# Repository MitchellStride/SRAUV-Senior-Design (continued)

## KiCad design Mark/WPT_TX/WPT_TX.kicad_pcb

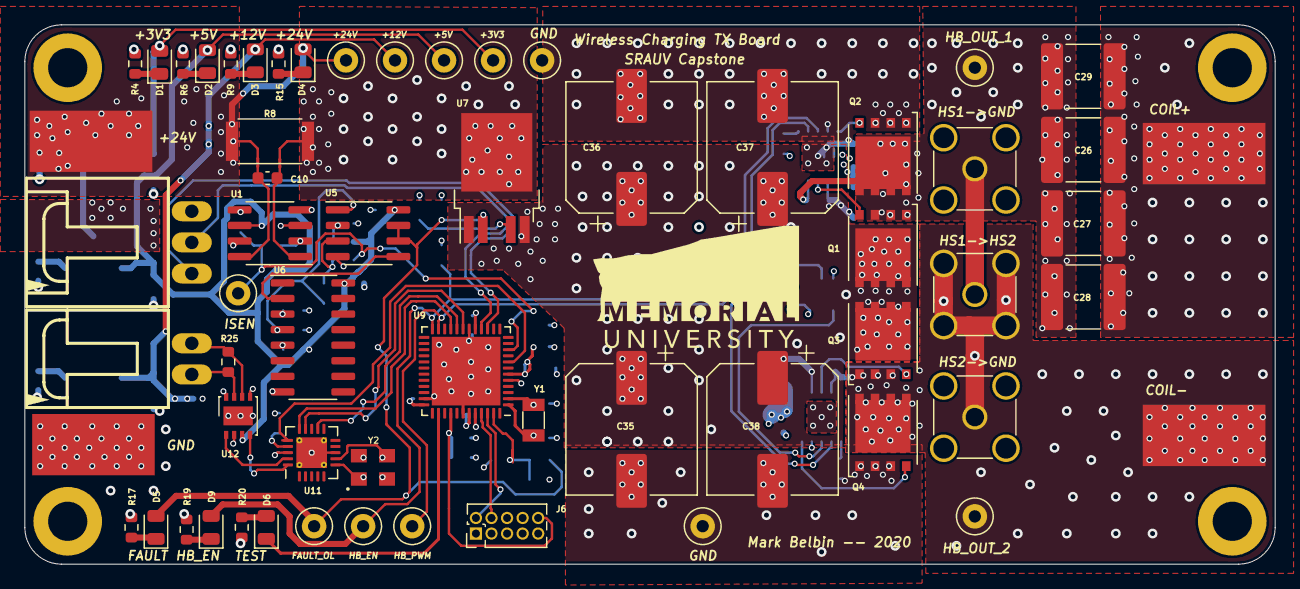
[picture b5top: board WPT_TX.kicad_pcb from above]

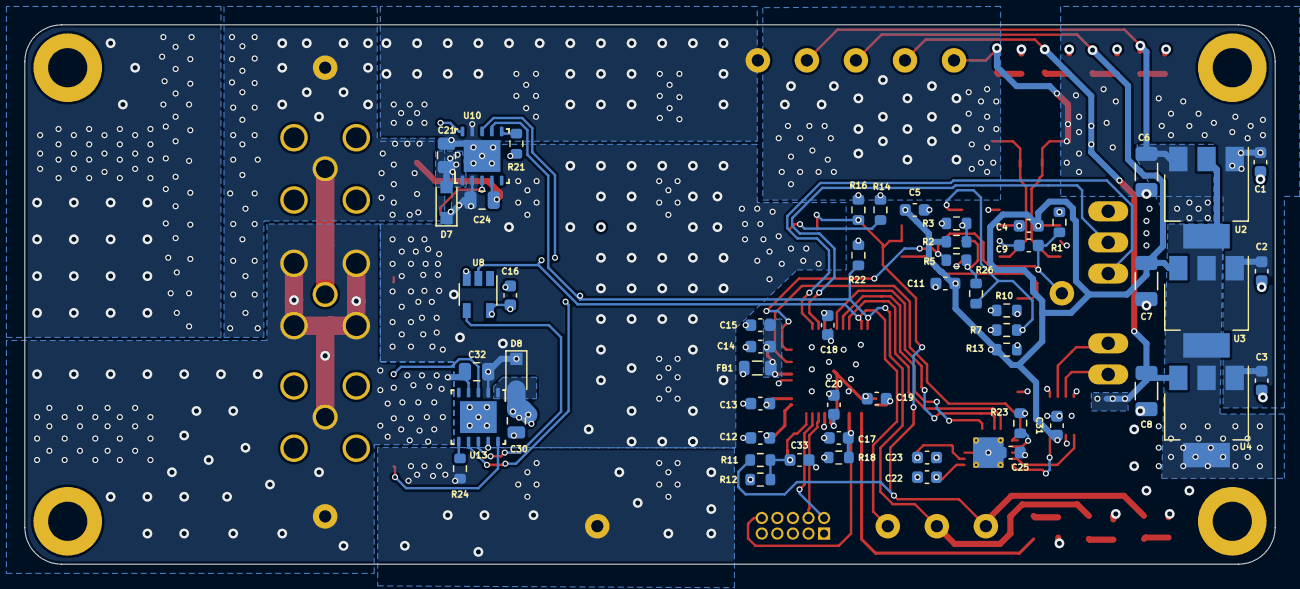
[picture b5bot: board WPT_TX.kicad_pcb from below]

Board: 4 copper layers, 102.0 x 44.0 mm, 121 parts (54 on the bottom side), 60 nets.

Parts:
C1, C2, C3, C4, C5, C9, C11, C14, C16, C17, C18, C19, C20, C25, C31, C33: 0.1u; C_0603_1608Metric
C6, C7, C8: 10u; C_1206_3216Metric
C10, C12, C13, C22, C23: 22p; C_0603_1608Metric
C15: 10u; C_0603_1608Metric
C21, C30: 0.47u; C_0805_2012Metric
C24, C32: 33n; C_0805_2012Metric
C26, C27, C28, C29: 100n; C_2220_5650Metric
C35, C36, C37, C38: 330u; CP_Elec_10x12.5
D1, D9: GREEN; LED_0805_2012Metric
D2: ORANGE; LED_0805_2012Metric
D3, D4: BLUE; LED_0805_2012Metric
D5: RED; LED_0805_2012Metric
D6: Orange; LED_0805_2012Metric
D7, D8: D_Schottky; D_SOD-323_HandSoldering
FB1: FB; L_0805_2012Metric
H1, H2, H3, H4: M3; MountingHole_3.2mm_M3_DIN965_Pad
J1, J2, J9, J10: Conn_01x01; SolderWirePad_single_SMD_5x10mm
J3, J4, J5: Conn_Coaxial; SMA_Amphenol_901-144_Vertical
J6: Conn_02x05_Odd_Even; PinHeader_2x05_P1.27mm_Vertical
J7: Conn_01x03; 70553-03
J8: Conn_01x04; 70553-02
NT1, NT2: Net-Tie_2; NetTie-2_SMD_Pad0.25mm
Q1, Q2, Q3, Q4: NMOS; TDSON-8-1
R1, R15: 2k; R_0603_1608Metric
R2, R7, R10, R11, R12, R13, R18, R21, R22, R23, R24, R26: 10k; R_0603_1608Metric
R3: 12k; R_0603_1608Metric
R4: 330; R_0603_1608Metric
R5, R9, R14, R16, R20: 1k; R_0603_1608Metric
R6, R17, R19: 680; R_0603_1608Metric
R8: 0.005; R_2512_Sense
R25: 120; R_0603_1608Metric
TP1, TP2, TP3, TP4, TP5, TP6, TP7, TP8, TP9, TP10, TP12, TP13: TestPoint; TestPoint_Loop_D1.80mm_Drill1.0mm_Beaded
U1: INA240A1D; SOIC-8_3.9x4.9mm_P1.27mm
U2: LM2937IMP-3.3; SOT-223-3_TabPin2
U3: LM2936-5.0; SOT-223-3_TabPin2
U4: LM2937IMP-12; SOT-223-3_TabPin2
U5: LMC6032; SOIC-8_3.9x4.9mm_P1.27mm
U6: CD4043BDR; SOIC-16_3.9x9.9mm_P1.27mm
U7: BTS6142DAUMA1; TO-252-4
U8: SN74LVC1G14DBV; TSOT-23-5
U9: ATSAMD21G16B-MFT; QFN-48-1EP_7x7mm_P0.5mm_EP5.6x5.6mm
U10, U13: LM5106; LM5106SD
U11: MCP2515-QFN20; QFN-20-1EP_4x4mm_P0.5mm_EP2.5x2.5mm_ThermalVias
U12: MCP2562-E-MF; DFN-8-1EP_3x3mm_P0.65mm_EP1.55x2.4mm
U14: Munlogo; MUNLOGO
Y1: 32.7680kHz; Crystal_SMD_3215-2pin_3.2x1.5mm
Y2: 8MHz; OSCCC320X250

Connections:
+3V3: C6.1, C16.1, C18.1, C19.1, C25.1, D1.2, FB1.2, J6.1, R18.1, R20.1, R23.1, TP1.1, U2.3, U8.5, U9.17, U9.36, U9.44, U11.18, U12.5
+5V: C4.1, C5.1, C7.1, C11.1, C31.1, D2.2, R2.2, R13.1, TP2.1, U1.6, U3.3, U5.8, U6.16, U12.3
+12V: C8.1, C21.1, C30.1, D3.2, D7.2, D8.2, TP3.1, U4.3, U10.1, U13.1
+24V: C1.1, C2.1, C3.1, D4.2, J1.1, NT1.1, R8.2, TP4.1, U2.1, U3.1, U4.1
/3V3_Filt: C14.1, C15.1, FB1.1, U9.6
/CANH: J8.1, R25.2, U12.7
/CANL: J8.2, R25.1, U12.6
/FAULT_OL: D5.2, R11.2, R16.2, TP6.1, U5.6, U5.7, U7.2
/FAULT_OL_MCU: C33.1, R11.1, R12.2, U9.47
/FAULT_OL_SR: U5.5, U6.2
/GATE1: Q1.2, U10.3
/GATE2: Q3.2, U13.3
/GATE3: Q2.2, U10.10
/GATE4: Q4.2, U13.10
/HBridge_EN: D9.2, R22.2, TP9.1, U9.24, U10.7, U13.7
/HBridge_PWM: TP8.1, U8.2, U9.23, U10.8
/HD: C24.1, C32.1, C35.1, C36.1, C37.1, C38.1, D7.1, D8.1, Q1.3, Q3.3, U7.1, U7.5, U10.2, U13.2
/HS_1: C24.2, C26.2, C27.2, C28.2, C29.2, J3.1, J5.1, Q1.1, Q2.3, TP12.1, U10.4
/HS_2: C32.2, J4.1, J5.2, J10.1, Q3.1, Q4.3, TP13.1, U13.4
/ISEN: C9.1, R1.1, R5.2, TP10.1, U9.10
/I_IN+: C10.2, NT1.2, U1.8
/I_IN-: C10.1, NT2.1, U1.1
/SPI0_CS: U9.8, U11.16
/SPI0_MISO: U9.21, U11.15
/SPI0_MOSI: U9.19, U11.14
/SPI0_SCLK: U9.20, U11.12
/SWCLK: J6.4, U9.45
/SWDIO: J6.2, U9.46
/UART_RX: J7.2, U9.16
/UART_TX: J7.1, U9.15
/VREF: R2.1, R3.2, U5.2
/~HBridge_PWM~: U8.4, U13.8
/~RST~: C17.1, J6.10, R18.2, U9.40
GND: C1.2, C2.2, C3.2, C4.2, C5.2, C6.2, C7.2, C8.2, C9.2, C11.2, C12.2, C13.2, C14.2, C15.2, C16.2, C17.2, C18.2, C19.2, C20.2, C21.2, C22.2, C23.2, C25.2, C30.2, C31.2, C33.2, C35.2, C36.2, C37.2, C38.2, J2.1, J3.2, J4.2, J6.3, J6.5, J6.9, J7.3, Q2.1, Q4.1, R3.1, R4.1, R6.1, R7.1, R9.1, R10.1, R12.1, R14.1, R15.1, R16.1, R17.1, R19.1, R21.1, R22.1, R24.1, TP5.1, TP7.1, U1.2, U1.3, U1.4, U1.7, U2.2, U3.2, U4.2, U5.4, U6.8, U8.3, U9.5, U9.18, U9.35, U9.42, U9.49, U10.9, U10.11, U11.8, U11.21, U12.2, U12.8, U12.9, U13.9, U13.11, Y2.2
unnamed: C12.1, U9.1, Y1.1
unnamed: C13.1, U9.2, Y1.2
unnamed: C20.1, U9.43
unnamed: C22.1, U11.6, Y2.1
unnamed: C23.1, U11.7, Y2.3
unnamed: C26.1, C27.1, C28.1, C29.1, J9.1
unnamed: D1.1, R4.2
unnamed: D2.1, R6.2
unnamed: D3.1, R9.2
unnamed: D4.1, R15.2
unnamed: D5.1, R17.2
unnamed: D6.1, U9.38
unnamed: D6.2, R20.2
unnamed: D9.1, R19.2
unnamed: NT2.2, R8.1, U7.3
unnamed: R1.2, U1.5
unnamed: R10.2, U6.3
unnamed: R13.2, U6.5
unnamed: R14.2, U7.4
unnamed: R21.2, U10.6
unnamed: R23.2, U11.17
unnamed: R24.2, U13.6
unnamed: R7.2, R26.1, U5.1, U6.4
unnamed: R5.1, R26.2, U5.3
unnamed: U11.19, U12.1
unnamed: U11.20, U12.4

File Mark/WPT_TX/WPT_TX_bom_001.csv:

Component,Description,Part,References,Value,Footprint,Quantity Per PCB,Digikey
1,,C_Small-Device,C1 C2 C3 C4 C5 C9 C11 C14 C16 C17 C18 C19 C20 C25 C31 C33,0.1u,C_0603_1608Metric,16,1276-1941-1-ND 1276-1258-1-ND
2,,C_Small-Device,C21 C30,0.47u,C_0805_2012Metric,2,478-10438-1-ND
3,,C_Small-Device,C26 C27 C28 C29,100n,C_2220_5650Metric,4,490-16696-1-ND
4,,C_Small-Device,C15,10u,C_0603_1608Metric,1,490-7201-1-ND
5,,C_Small-Device,C6 C7 C8,10u,C_1206_3216Metric,3,1276-6767-1-ND
6,,C_Small-Device,C10 C12 C13 C22 C23,22p,C_0603_1608Metric,5,720-VJ0603A220JXBACCT-ND
7,"Polarized capacitor, US symbol",CP1,C35 C36 C37 C38,330u,CP_Elec_10x12.5,4,493-13765-1-ND
8,,C_Small-Device,C24 C32,33n,C_0805_2012Metric,2,445-172691-1-ND
9,,LED-Device,D3 D4,BLUE,LED_0805_2012Metric,2,160-1579-1-ND
10,,D_Schottky-Device,D7 D8,D_Schottky,D_SOD-323_HandSoldering,2,641-1786-1-ND
11,,LED-Device,D1 D9,GREEN,LED_0805_2012Metric,2,160-1423-1-ND
12,,LED-Device,D2 D6,ORANGE,LED_0805_2012Metric,2,160-1413-1-ND
13,,LED-Device,D5,RED,LED_0805_2012Metric,1,475-1415-1-ND
14,,Ferrite_Bead_Small-Device,FB1,FB,L_0805_2012Metric,1,490-9706-1-ND
15,,Conn_01x01-Connector_Generic,J1 J2 J9 J10,Conn_01x01,SolderWirePad_single_SMD_5x10mm,4,
16,,Conn_01x03-Connector_Generic,J7,Conn_01x03,70553-03,1,WM4154-ND
17,,Conn_01x02-Connector_Generic,J8,Conn_01x04,70553-02,1,WM4900-ND
18,,Conn_02x05_Odd_Even-Connector_Generic,J6,Conn_02x05_Odd_Even,PinHeader_2x05_P1.27mm_Vertical,1,1175-1627-ND
19,,Conn_Coaxial-Connector,J3 J4 J5,Conn_Coaxial,SMA_Amphenol_901-144_Vertical,3,WM17068-ND
20,,Net-Tie_2-Device,NT1 NT2,Net-Tie_2,NetTie-2_SMD_Pad0.25mm,2,
21,,Q_NMOS_SGD-Device,Q1 Q2 Q3 Q4,NMOS,TDSON-8-1,4,448-IAUC70N08S5N074ATMA1CT-ND
22,,R_US-Device,R8,0.005,R_2512_Sense,1,YAG6124CT-ND
23,,R_US-Device,R2 R7 R10 R11 R12 R13 R18 R21 R22 R23 R24 R26,10k,R_0603_1608Metric,12,RHM10KDCT-ND
24,,R_US-Device,R25,120,R_0603_1608Metric,1,P120BYTR-ND
25,,R_US-Device,R3,12k,R_0603_1608Metric,1,P12KDBCT-ND
26,,R_US-Device,R5 R9 R14 R16 R20,1k,R_0603_1608Metric,5,RHM1.0KDCT-ND
27,,R_US-Device,R1 R15,2k,R_0603_1608Metric,2,541-2790-1-ND
28,,R_US-Device,R4,330,R_0603_1608Metric,1,RHM330DCT-ND
29,,R_US-Device,R6 R17 R19,680,R_0603_1608Metric,3,RHM680DCT-ND
30,IC MCU 32BIT 64KB FLASH 48QFN,ATSAMD21G16B-MFT,U9,ATSAMD21G16B-MFT,QFN-48-1EP_7x7mm_P0.5mm_EP5.6x5.6mm,1,ATSAMD21G18A-MF-ND
31,,BTS6142DAUMA1,U7,BTS6142DAUMA1,TO-252-4,1,BTS6142DAUMA1CT-ND
32,,CD4043BDR,U6,CD4043BDR,SOIC-16_3.9x9.9mm_P1.27mm,1,296-31496-1-ND
33,,INA240A1D-Amplifier_Current,U1,INA240A1D,SOIC-8_3.9x4.9mm_P1.27mm,1,296-48837-ND
34,,LM2936-5.0-Regulator_Linear,U3,LM2936-5.0,SOT-223-3_TabPin2,1,296-37374-1-ND
35,,LM2937xMP-Regulator_Linear,U4,LM2937IMP-12,SOT-223-3_TabPin2,1,LM2937IMP-12/NOPBCT-ND
36,,LM2937xMP-Regulator_Linear,U2,LM2937IMP-3.3,SOT-223-3_TabPin2,1,LM2937IMPX-3.3/NOPBCT-ND
37,,LM5106SD_NOPB,U10 U13,LM5106,LM5106SD,2,LM5106SD/NOPBCT-ND
38,,LMC6082-Amplifier_Operational,U5,LMC6032,SOIC-8_3.9x4.9mm_P1.27mm,1,296-49646-1-ND
39,,MCP2515-QFN20,U11,MCP2515-QFN20,QFN-20-1EP_4x4mm_P0.5mm_EP2.5x2.5mm_ThermalVias,1,MCP2515-E/ML-ND
40,,MCP2562-E-MF-Interface_CAN_LIN,U12,MCP2562-E-MF,DFN-8-1EP_3x3mm_P0.65mm_EP1.55x2.4mm,1,MCP2562-E/MF-ND
41,,Munlogo,U14,Munlogo,MUNLOGO,1,
42,,SN74LVC1G14DBV-74xGxx,U8,SN74LVC1G14DBV,TSOT-23-5,1,296-35944-1-ND
43,,Crystal-Device,Y1,32.7680kHz,Crystal_SMD_3215-2pin_3.2x1.5mm,1,‎XC1656CT-ND‎
44,,Crystal_GND2_Small-Device,Y2,8MHz,OSCCC320X250,1,2151-RH100-8.000-20-3050-EXT-TRCT-ND
,,,,,,,
,,,,,,,
,,,,,,,
,,,,,,,
,,,,,,,
Component Groups:,44,,,,,,
Component Count:,105,,,,,,
Fitted Components:,105,,,,,,
Number of PCBs:,1,,,,,,
Total components:,105,,,,,,
Schematic Version:,1,,,,,,
Schematic Date:,2020-11-08,,,,,,
PCB Variant:,[u'default'],,,,,,
BoM Date:,2020-11-23 21:35,,,,,,
Schematic Source:,D:\AUV Capstone\AUV-Senior-Design\Mark\WPT_TX\WPT_TX.sch,,,,,,
KiCad Version:,Eeschema (5.1.8)-1,,,,,,

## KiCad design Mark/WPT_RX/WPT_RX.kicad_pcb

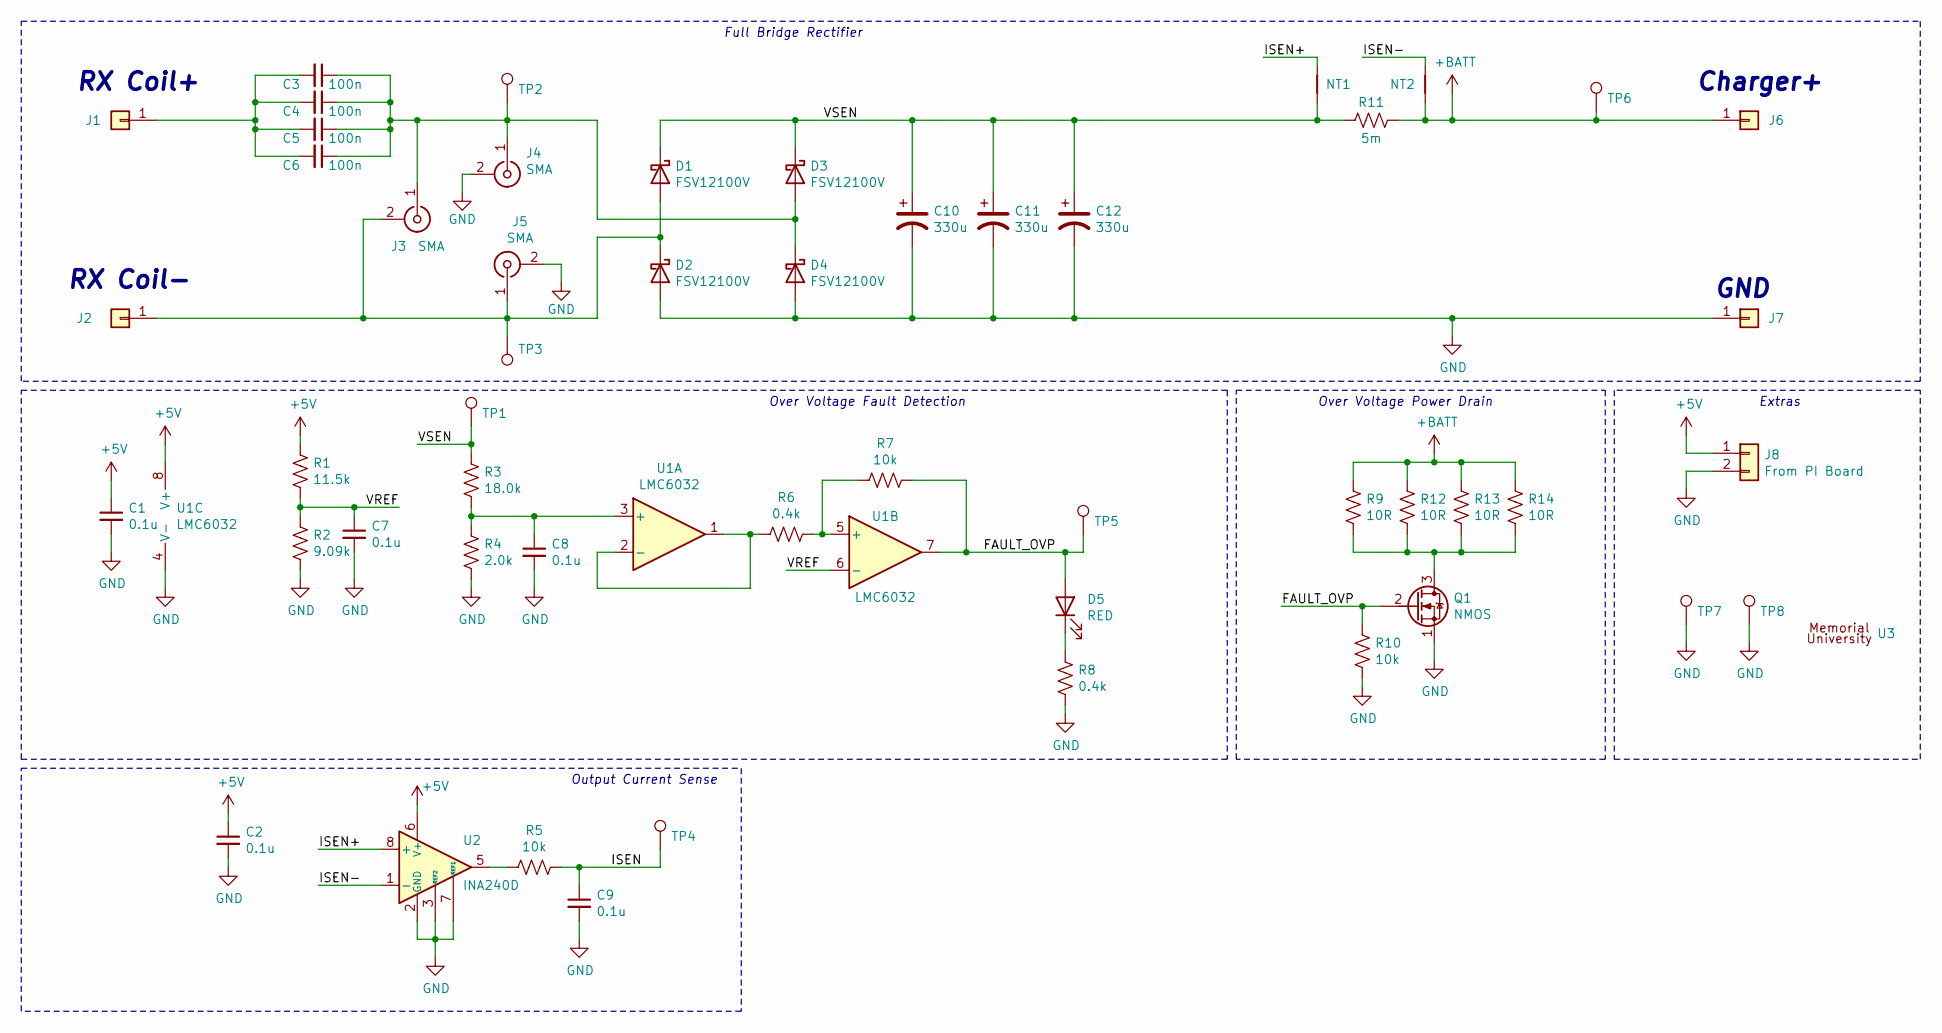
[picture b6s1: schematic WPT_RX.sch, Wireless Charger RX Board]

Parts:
C1, C2, C7, C8, C9: 0.1u; C_0603_1608Metric; Digikey 1276-1258-1-ND
C3, C4, C5, C6: 100n; C_2220_5650Metric; Digikey 490-16696-1-ND
C10, C11, C12: 330u; CP_Elec_10x12.5; Digikey 493-13765-1-ND
D1, D2, D3, D4: FSV12100V; TO-277B; Digikey FSV12100VCT-ND
D5: RED; LED_0805_2012Metric; Digikey 475-1415-1-ND
J1, J2, J6, J7: Conn_01x01; SolderWirePad_single_SMD_5x10mm
J3, J4, J5: SMA; SMA_Amphenol_901-144_Vertical; Digikey WM17068-ND
J8: From PI Board; 70553-02; Digikey WM4900-ND
NT1, NT2: Net-Tie_2; NetTie-2_SMD_Pad0.25mm
Q1: NMOS; TDSON-8-1; Digikey 448-IAUC70N08S5N074ATMA1CT-ND
R1: 11.5k; R_0603_1608Metric; Digikey RMCF0603FT11K5CT-ND
R2: 9.09k; R_0603_1608Metric; Digikey RMCF0603FT9K09CT-ND
R3: 18.0k; R_0603_1608Metric; Digikey P18KDBCT-ND
R4: 2.0k; R_0603_1608Metric; Digikey 541-2790-1-ND
R5, R7, R10: 10k; R_0603_1608Metric; Digikey RHM10KDCT-ND
R6, R8: 0.4k; R_0603_1608Metric; Digikey PAT400ACT-ND
R9, R12, R13, R14: 10R; TO-220F-2_Horizontal_TabDown; Digikey PWR221T-50-10R0F-ND
R11: 5m; R_2512_Sense; Digikey YAG6124CT-ND
TP1, TP2, TP3, TP4, TP5, TP6: TestPoint; TestPoint_Loop_D1.80mm_Drill1.0mm_Beaded; Digikey 36-5117-ND
TP7, TP8: TestPoint; TestPoint_Loop_D1.80mm_Drill1.0mm_Beaded; Digikey 36-5001-ND
U1: LMC6032; SOIC-8_3.9x4.9mm_P1.27mm
U2: INA240D; SOIC-8_3.9x4.9mm_P1.27mm; Digikey 296-48837-ND
U3: MUN; MUNLOGO

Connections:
+5V: C1.1, C2.1, J8.1, R1.1, U1.8 (V+), U2.6 (V+)
+BATT: J6.1, NT2.1, R9.1, R11.2, R12.1, R13.1, R14.1, TP6.1
/FAULT_OVP: D5.2 (A), Q1.2 (G), R7.1, R10.1, TP5.1, U1.7
/ISEN: C9.1, R5.2, TP4.1
/ISEN+: NT1.1, U2.8 (+); also elsewhere on the board
/ISEN-: NT2.2, U2.1 (-); also elsewhere on the board
/VREF: C7.1, R1.2, R2.1, U1.6 (-)
/VSEN: C10.1, C11.1, C12.1, D1.1 (K), D3.1 (K), NT1.2, R3.1, R11.1, TP1.1
GND: C1.2, C2.2, C7.2, C8.2, C9.2, C10.2, C11.2, C12.2, D2.2 (A), D4.2 (A), J4.2 (Ext), J5.2 (Ext), J7.1, J8.2, Q1.1 (S), R2.2, R4.2, R8.1, R10.2, TP7.1, TP8.1, U1.4 (V-), U2.2 (GND), U2.3 (REF2), U2.4 (GND), U2.7 (REF1)
unnamed: C3.1, C4.1, C5.1, C6.1, D3.2 (A), D4.1 (K), J3.1 (In), J4.1 (In), TP2.1
unnamed: C3.2, C4.2, C5.2, C6.2, J1.1
unnamed: C8.1, R3.2, R4.1, U1.3 (+)
unnamed: D1.2 (A), D2.1 (K), J2.1, J3.2 (Ext), J5.1 (In), TP3.1
unnamed: D5.1 (K), R8.2
unnamed: Q1.3 (D), R9.2, R12.2, R13.2, R14.2
unnamed: R5.1, U2.5
unnamed: R6.1, R7.2, U1.5 (+)
unnamed: R6.2, U1.1, U1.2 (-)

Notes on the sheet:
RX Coil+
RX Coil-
Charger+
GND
Output Current Sense
Over Voltage Fault Detection
Over Voltage Power Drain
Extras
Full Bridge Rectifier

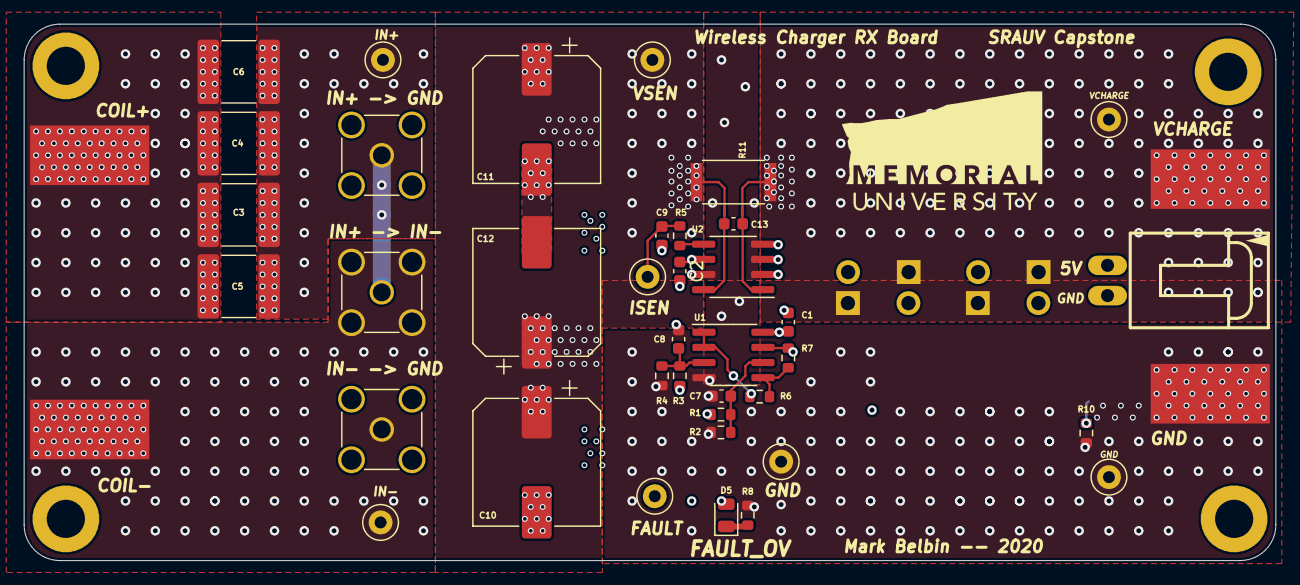
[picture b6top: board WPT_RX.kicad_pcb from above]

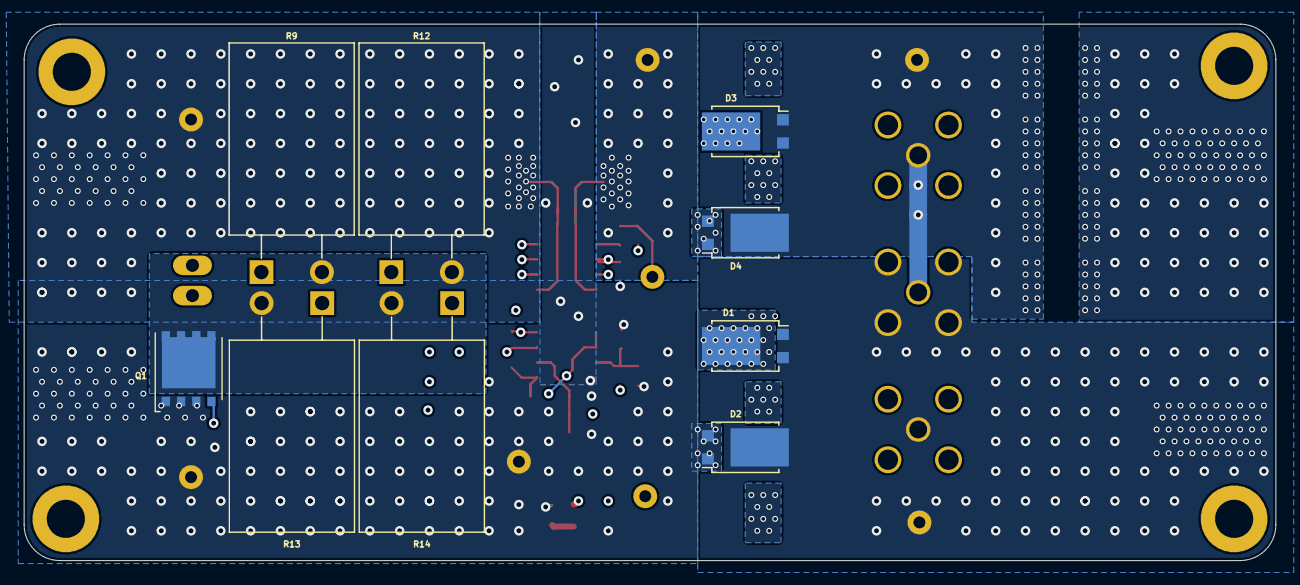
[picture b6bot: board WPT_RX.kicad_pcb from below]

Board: 4 copper layers, 105.0 x 45.0 mm, 58 parts (9 on the bottom side), 18 nets.

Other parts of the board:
C13: 0.1u; C_0603_1608Metric
H1, H2, H3, H4: M3; MountingHole_3.2mm_M3_DIN965_Pad

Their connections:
/ISEN+: C13.1; also elsewhere on the board
/ISEN-: C13.2; also elsewhere on the board

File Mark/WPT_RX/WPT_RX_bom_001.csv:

Component,Description,Part,References,Value,Footprint,Quantity Per PCB,Datasheet,Digikey
1,"Unpolarized capacitor, small symbol",C_Small,C1 C2 C7 C8 C9 C13,0.1u,C_0603_1608Metric,6,~,1276-1258-1-ND
2,"Unpolarized capacitor, small symbol",C_Small,C3 C4 C5 C6,100n,C_2220_5650Metric,4,~,490-16696-1-ND
3,"Polarized capacitor, US symbol",CP1,C10 C11 C12,330u,CP_Elec_10x12.5,3,~,493-13765-1-ND
4,Schottky diode,D_Schottky,D1 D2 D3 D4,FSV12100V,TO-277B,4,~,FSV12100VCT-ND
5,Light emitting diode,LED,D5,RED,LED_0805_2012Metric,1,~,475-1415-1-ND
6,"Generic connector, single row, 01x01, script generated (kicad-library-utils/schlib/autogen/connector/)",Conn_01x01,J1 J2 J6 J7,Conn_01x01,SolderWirePad_single_SMD_5x10mm,4,~,
7,"Generic connector, single row, 01x02, script generated (kicad-library-utils/schlib/autogen/connector/)",Conn_01x02,J8,From PI Board,70553-02,1,~,WM4900-ND
8,"coaxial connector (BNC, SMA, SMB, SMC, Cinch/RCA, ...)",Conn_Coaxial,J3 J4 J5,SMA,SMA_Amphenol_901-144_Vertical,3, ~,WM17068-ND
9,"Net tie, 2 pins",Net-Tie_2,NT1 NT2,Net-Tie_2,NetTie-2_SMD_Pad0.25mm,2,~,
10,"N-MOSFET transistor, source/gate/drain",Q_NMOS_SGD,Q1,NMOS,TDSON-8-1,1,~,448-IAUC70N08S5N074ATMA1CT-ND
11,"Resistor, US symbol",R_US,R6 R8,0.4k,R_0603_1608Metric,2,~,PAT400ACT-ND
12,"Resistor, US symbol",R_US,R9 R12 R13 R14,10R,TO-220F-2_Horizontal_TabDown,4,~,PWR221T-50-10R0F-ND
13,"Resistor, US symbol",R_US,R5 R7 R10,10k,R_0603_1608Metric,3,~,RHM10KDCT-ND
14,"Resistor, US symbol",R_US,R1,11.5k,R_0603_1608Metric,1,~,RMCF0603FT11K5CT-ND
15,"Resistor, US symbol",R_US,R3,18.0k,R_0603_1608Metric,1,~,P18KDBCT-ND
16,"Resistor, US symbol",R_US,R4,2.0k,R_0603_1608Metric,1,~,541-2790-1-ND
17,"Resistor, US symbol",R_US,R11,5m,R_2512_Sense,1,~,YAG6124CT-ND
18,"Resistor, US symbol",R_US,R2,9.09k,R_0603_1608Metric,1,~,RMCF0603FT9K09CT-ND
19,"High- and Low-Side, Bidirectional, Zero-Drift, Current-Sense Amplifier With Enhanced PWM Rejection, 20V/V, SOIC-8",INA240A1D,U2,INA240D,SOIC-8_3.9x4.9mm_P1.27mm,1,http://www.ti.com/lit/ds/symlink/lmc6082.pdf,296-48837-ND
20,"Precision CMOS Dual Operational Amplifier, DIP-8/SOIC-8",LMC6082,U1,LMC6032,SOIC-8_3.9x4.9mm_P1.27mm,1,http://www.ti.com/lit/ds/symlink/lmc6082.pdf,LMC6032IMX/NOPBCT-ND
21,,Munlogo,U3,MUN,MUNLOGO,1,,





Component Groups:,21
Component Count:,46
Fitted Components:,46
Number of PCBs:,1
Total components:,46
Schematic Version:,001
Schematic Date:,2020-11-13
PCB Variant:,[u'default']
BoM Date:,2020-11-23 9:48:27 PM
Schematic Source:,D:\AUV Capstone\AUV-Senior-Design\Mark\WPT_RX\WPT_RX.sch
KiCad Version:,Eeschema (5.1.8)-1

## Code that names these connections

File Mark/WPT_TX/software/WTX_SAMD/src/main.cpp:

const int HBridge_PWM = X; //Add pins here
const int HBridge_EN = X;
const int ISEN = A4;
float current = 0;

void setup() {
  pinMode(HBridge_PWM, OUTPUT);
  pinMode(HBridge_EN, OUTPUT);
  delay(1);  //Wait after powering on.


  digitalWrite(HBridge_EN, 1);
  analogWrite(HBridge_PWM, 127); //TODO edit this to use the tone lib to set freq 

  Serial.begin(9600);
}

void loop() {
  current = analogRead(ISEN);
  current = current * (5.0 / 1023.0);   //TODO, Edit conversion to be conrrect
  Serial.println(current);
}

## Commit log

2020-06-10 Added folder structure and first pcb
    Repo Creation
2020-06-10 first push - it's really incomplete - just wanna get it off my work computer
2020-06-16 minor schematic update + inrush sim
2020-06-16 updated sim
2020-06-22 Weekends work. Final component selection then ready for review :)
    huge oof
2020-06-24 batt-management sheet updates
2020-06-26 Minor schematic organization changes
2020-06-30 for review at 2pm
2020-07-12 more work
2020-07-12 more changes :)
2020-07-18 ready for review? maybe. (not really)
2020-07-19 ready for review
2020-07-23 some layout
2020-08-04 push
2020-08-14 last push from tesla computer
2020-10-24 First Official Schematic Release
    yeet
2020-10-26 Created Projects
    - Made blank TX/RX WPT board projects.
    - Also made a folder for TX firmware, going to shoot for some telemetry so its legittt.
2020-10-26 Sims
    - Added current sims.
    - New sims will live here
2020-10-26 Started Schematics
    - Started on the schs
    - Going to do more work on this after work tomorrow.
    - Goal is to be done TX / RX before the election and the resulting civil war.
2020-10-27 Sims and Sch
    - Played around with the sims
    - Selected FETs for TX board, did calcs to make sure losses are good. (They are reallyyyyy low, even for 200kHz switching)
2020-10-28 Resonance Sims
    - Looking at what happens with series capacitors.
    - It looks reallllyyyyyy good.
    - Some big cavets are the dependency on k and frequency.
    - As well, open load blows up the the TX, perhaps can add a current sense to be sure it won't overload.
2020-10-28 More Sims
    - Looking at frequency variation.
    - Confirmed SS compensation.
    - Better AC analysis, legit this time
2020-10-31 Copied Sims
    - Brought over sims from Franks folder to mine since libraries are folder dependent, not even relative path
2020-10-31 Updated Simple Sim
    - Replaced current source with resistor, current source creates weird affects.
    - Tried split cap compensation, DOES NOT WORK. (Another loss for symmetry)
    - Updated operating frequnecy
2020-10-31 RX Overvoltage SIMs
    - Created successful bleed resistor circuit to apply a proper load and output voltage during charger startup.
    - Next step is to try and protect for a true open load on the TX side.
2020-11-02 Updated Fault Circuits
    - Added in circuit for open load detection.
    - Removed schmitt trigger symbols and replaced with opamp circuits that will actually be used on the board.
    - Added in current sense circuit with actual INA240 model.
2020-11-02 Updated Sim
    - Replaced series cap ESR with anticiapted ESR after selecting series caps.
    - Still need to select input and output caps, add in their appropriate ESR
2020-11-02 Cleaned up Sim Schematic
    - Added more text, boxed in the voltage sources
2020-11-02 first (hopefully final) routing pass
2020-11-09 TX Schematic
    - Finished up TX schematic.
2020-11-09 TX BOM / Footprints
    - Added all BOM and footprint selections to components.
    - Imported netlist into pcb file.
    - Also 3D models!!
2020-11-09 small tweaks to thermal reliefs on planes
2020-11-10 Added input caps
    - Forgot input capacitors, oops
    - Updated sim based on cap selection, achieving 87% efficiency, low loss on caps!
2020-11-13 Finished RX Schematic
    - Finsihed RX schematic
    - Completed RX BOM
    - Added all footprints
    - Only power resistor 3D model is outstanding, will add that later
2020-11-13 lowered kicad version. Also tided up routing DRC cleared.
2020-11-15 Initial Layout
    - Started on layout, board shape.
    - Probably will need to get a little larger, but its pretty good
2020-11-15 Layout
    - Finished expected layout. Going for routing next.
2020-11-15 Some Routing
    - Most non-plane routing is complete
2020-11-15 Routing Final
    - Finished all routing, should work out fine.
    - All that's left is silkscreen
2020-11-16 Silkscreen & Touchups
    - Board is finished!
    - Fixed up silkscreen and some placement, looks good.
2020-11-16 RX Layout
    - Completed layout
    - Also cleaned up some silkscreen since I was in the zone.
2020-11-16 More Layout
    - Reduced board length, should reduce board cost.
2020-11-16 Finished RX Board
    - Layout and routing complete.
    - Silk looks good.
    - All 3D models are in there.
2020-11-17 Updated TX
    - Changed OL detector to a non inverting schmitt trigger.
    - Updated routing, added more vias
2020-11-17 Updated SIM
    - Changed sim ol detector to match TX board
2020-11-17 Gerbers
    - Generated gerbers
    - Changed TX board size to 45x100mm to match RX board.
    - Ordered PCBs like the impaitent bastard I am
2020-11-20 routing V2
2020-11-22 routing v2.1.
2020-11-24 Created WPT BOMs
    - Created TX and RX BOMs
2020-11-29 3D Models
    - Generated 3D Models of boards
2020-11-29 chum bucket 3d model
    - Exported 3D model of board
2020-12-24 post-BOM order
2021-01-14 Updated Schematic and working bom .csv file
2021-01-14 Sch label net changes to global tags
2021-01-16 Pi4 Remake Done
2021-01-17 Added Pi board gerbers, rgb board, leak board, eth board,
2021-01-17 fixed gerbs on pi board
2021-01-18 Order snapshot and bom order
2021-02-01 Created 3D Model
    - Made a 3D model of the Pi Expansion board
2021-02-23 added software notes and programs
2021-02-23 added depth sense example
    added folder for depth sense tests
    issues, python 2 to 3 and address initilized in imported file?
2021-02-27 programmed firmware
2021-03-17 pushin mod pdf and some code
2021-03-18 Update test code to fix inf can loop issue
2021-03-28 Added project images
2021-03-28 added pics, pres, and readme changes
2021-03-28 added one pic to readme error
2021-04-07 added arduino version
2021-04-08 working on code
2021-04-08 submitted latest duino code
2021-05-22 any remaining code changes and readme for boards.txt change
    Added slack post to readme to remember how we programmed it.
2021-05-23 WPT Simulation Updates
    - Brought load down to 50W, played around with freq.
